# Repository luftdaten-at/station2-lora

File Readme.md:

# Luftdaten.at Station v2.3 LoRa

## Hardware Setup

## Micropython Setup

Using esptool.py you can erase the flash with the command:
`esptool.py --port /dev/ttyUSB0 erase_flash`

And then deploy the new firmware using:
`esptool.py --chip esp32 --port /dev/ttyUSB0 write_flash -z 0x1000 esp32-20180511-v1.9.4.bin`

Once you have the firmware on the device you can access the REPL (Python prompt) over UART0 (GPIO1=TX, GPIO3=RX), which might be connected to a USB-serial convertor, depending on your board. The baudrate is 115200.

## Installation

Save config-sample.json as config.json and add the The Things Network settings.

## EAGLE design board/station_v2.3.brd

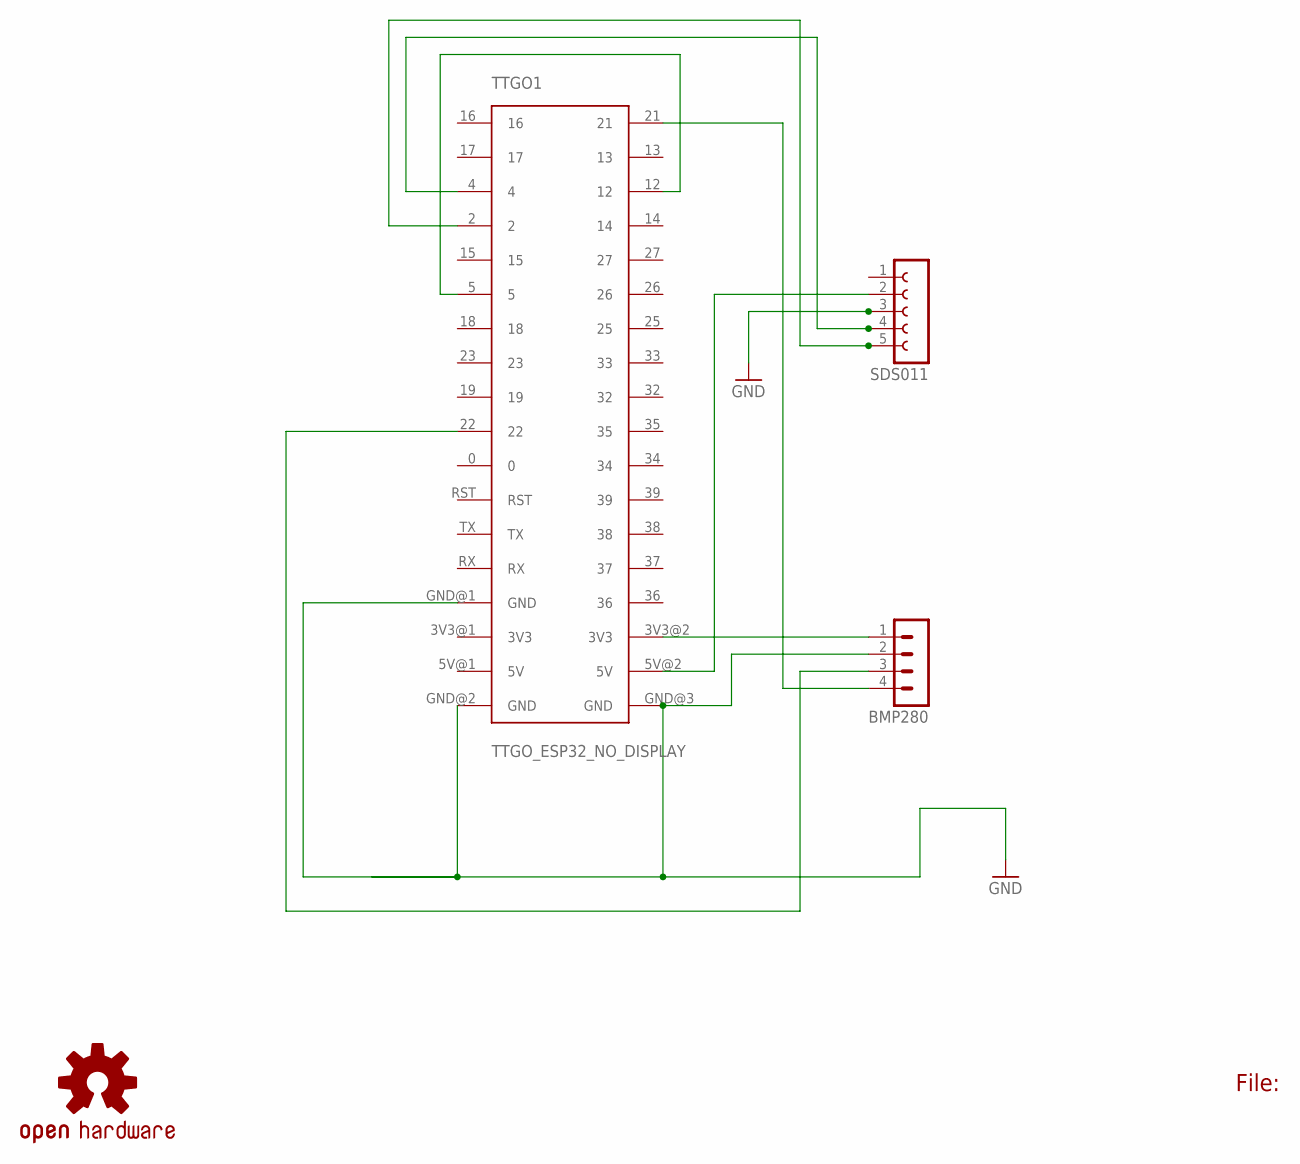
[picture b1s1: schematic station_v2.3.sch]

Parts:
BMP280: MA04-1
LOGO2: OSHW-LOGOM; OSHW-LOGO-M
SDS011: FE05-1
TTGO1: TTGO_ESP32_NO_DISPLAY

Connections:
GND: BMP280.2, SDS011.3, TTGO1.GND@1 (GND), TTGO1.GND@2 (GND), TTGO1.GND@3 (GND)
GPIO0: SDS011.5, TTGO1.2
GPIO2: SDS011.4, TTGO1.4
unnamed: SDS011.2, TTGO1.5V@2 (5V)
unnamed: BMP280.1, TTGO1.3V3@2 (3V3)
unnamed: TTGO1.5, TTGO1.12
unnamed: BMP280.3, TTGO1.22
unnamed: BMP280.4, TTGO1.21

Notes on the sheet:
File:

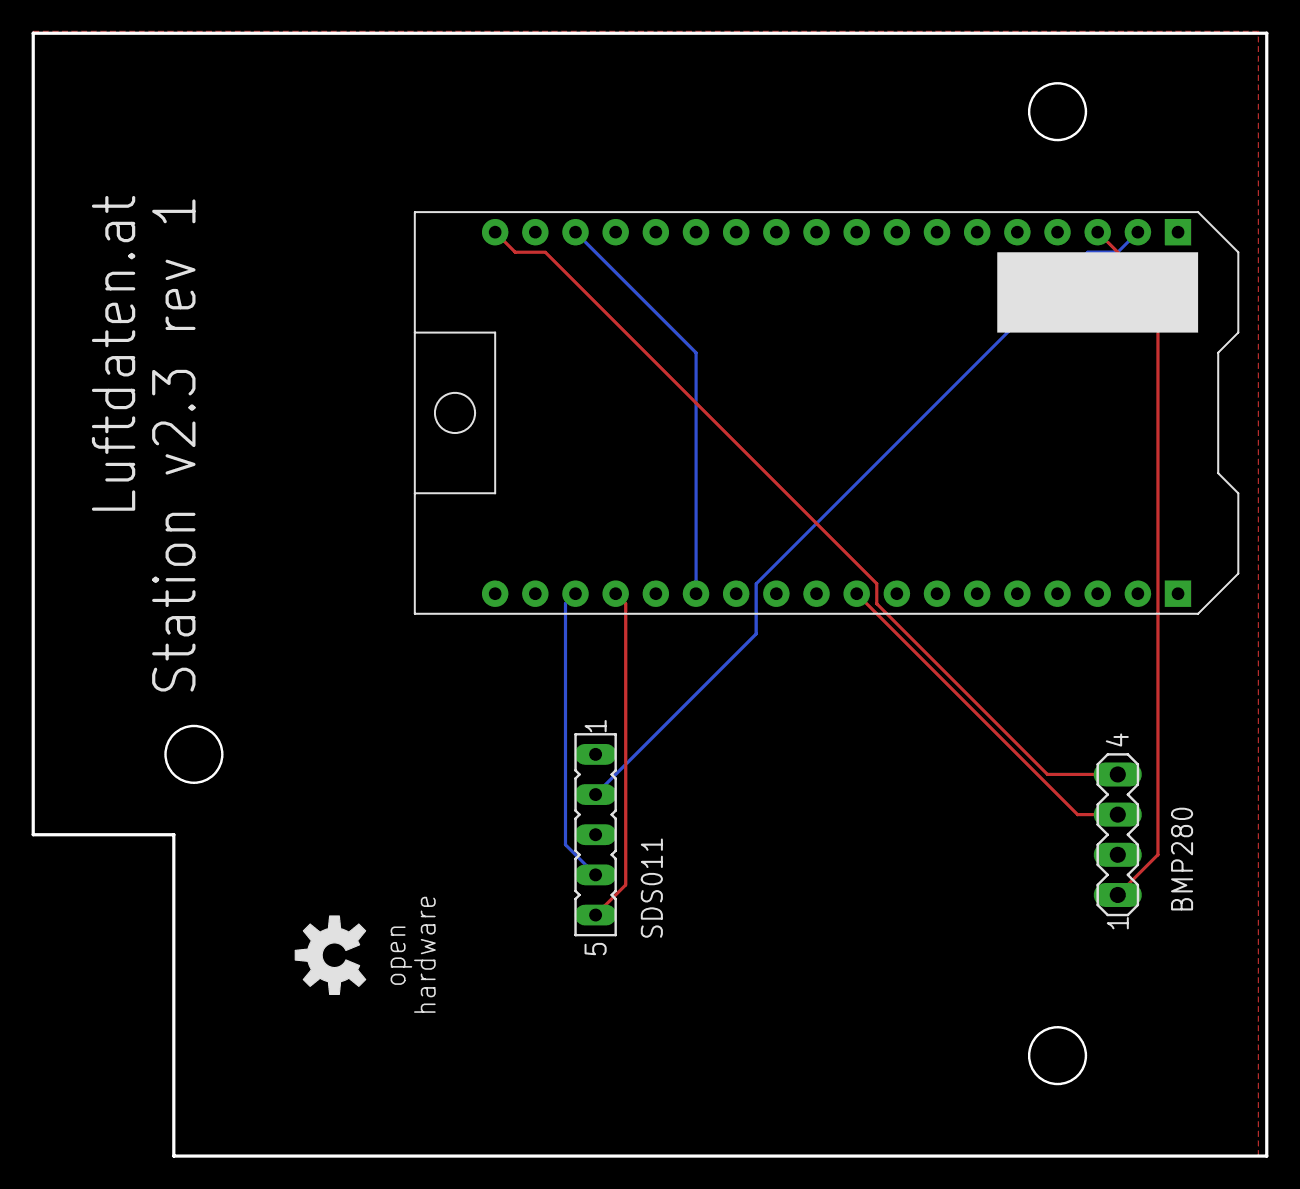
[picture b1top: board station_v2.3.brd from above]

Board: 2 copper layers, 78.0 x 71.0 mm, 4 parts (0 on the bottom side), 8 nets.

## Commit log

2020-02-09 first version
2020-02-09 update gitignore
    added macos filetypes to gitignore
2021-02-17 new folder structure
2021-02-17 add MIT license
2021-02-17 edit gitignore
2021-02-17 add board files
2021-02-17 added case files
2021-02-18 change to MIT License
2021-02-20 readme update

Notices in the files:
parts and their libraries:
SparkFun-Aesthetics: Licensing: Creative Commons ShareAlike 4.0 International - https://creativecommons.org/licenses/by-sa/4.0
